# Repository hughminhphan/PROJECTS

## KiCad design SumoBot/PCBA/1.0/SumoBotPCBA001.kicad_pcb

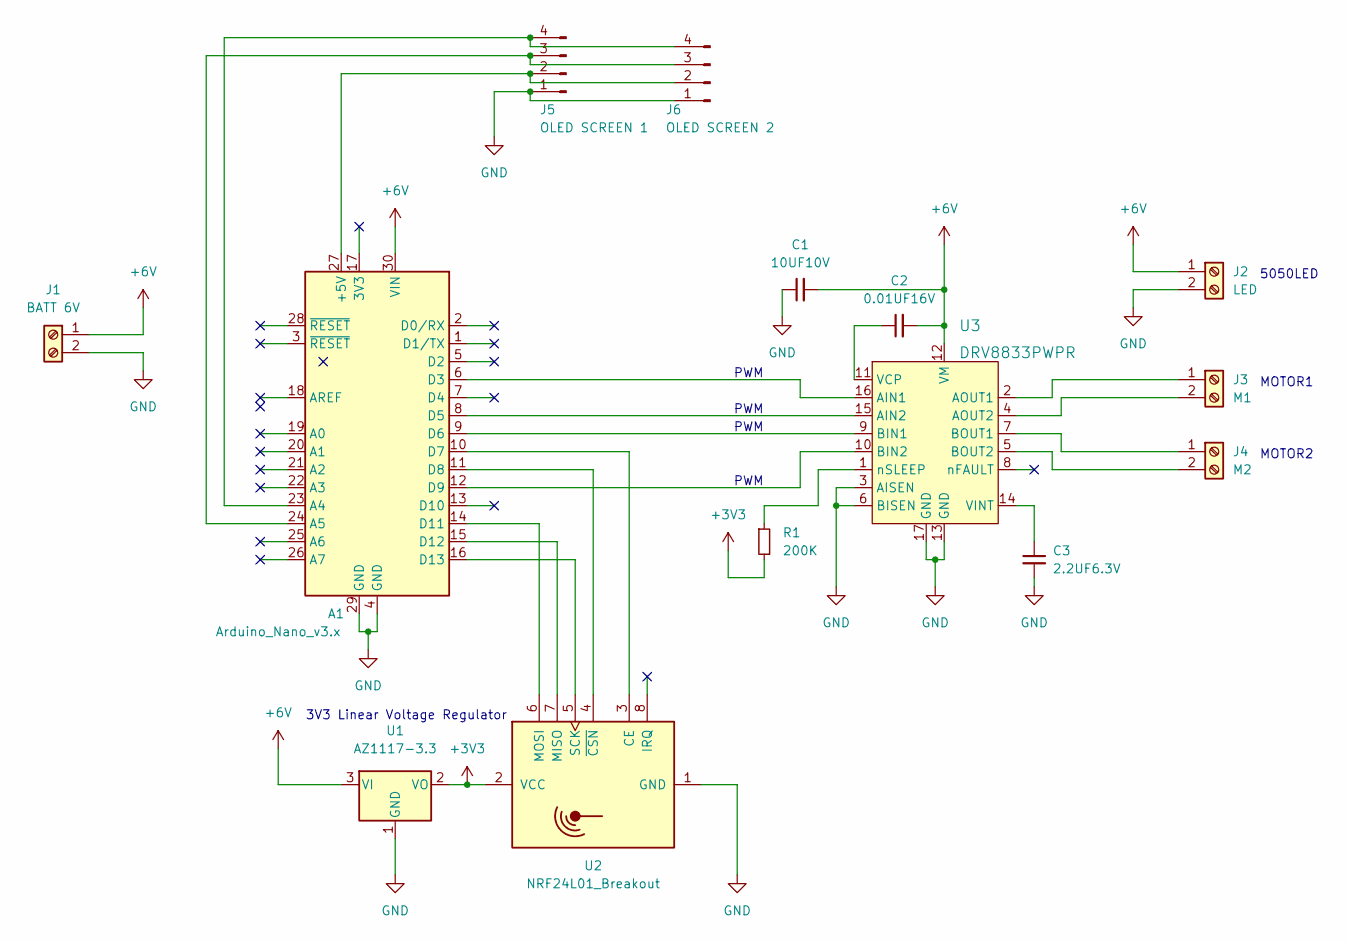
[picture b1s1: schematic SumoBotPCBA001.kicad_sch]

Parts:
A1: Arduino_Nano_v3.x; Arduino_Nano
C1: 10UF10V; C_0805_2012Metric_Pad1.18x1.45mm_HandSolder
C2: 0.01UF16V; C_0805_2012Metric_Pad1.18x1.45mm_HandSolder
C3: 2.2UF6.3V; C_0805_2012Metric_Pad1.18x1.45mm_HandSolder
J1: BATT 6V; TerminalBlock_bornier-2_P5.08mm
J2: LED; TerminalBlock_bornier-2_P5.08mm
J3: M1; TerminalBlock_bornier-2_P5.08mm
J4: M2; TerminalBlock_bornier-2_P5.08mm
J5: OLED SCREEN 1; PinSocket_1x04_P2.54mm_Vertical
J6: OLED SCREEN 2; PinSocket_1x04_P2.54mm_Vertical
R1: 200K; R_0805_2012Metric_Pad1.20x1.40mm_HandSolder
U1: AZ1117-3.3; SOT-89-3_Handsoldering
U2: NRF24L01_Breakout; nRF24L01_Breakout
U3: DRV8833PWPR; TSSOP-16-1EP_W4.40mm; MPN DRV8833PWPR; Digi-Key_PN 296-29434-1-ND

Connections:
+3V3: R1.2, U1.2 (VO), U2.2 (VCC)
+6V: A1.30 (VIN), C1.2, C2.2, J1.1, J2.1, U1.3 (VI), U3.12 (VM)
GND: A1.4 (GND), A1.29 (GND), C1.1, C3.2, J1.2, J2.2, J5.1, J6.1, U1.1 (GND), U2.1 (GND), U3.3 (AISEN), U3.6 (BISEN), U3.13 (GND), U3.17 (GND)
unnamed: A1.6 (D3), U3.16 (AIN1)
unnamed: A1.8 (D5), U3.15 (AIN2)
unnamed: A1.9 (D6), U3.9 (BIN1)
unnamed: A1.10 (D7), U2.3 (CE)
unnamed: A1.11 (D8), U2.4 (~CSN)
unnamed: A1.12 (D9), U3.10 (BIN2)
unnamed: A1.14 (D11), U2.6 (MOSI)
unnamed: A1.15 (D12), U2.7 (MISO)
unnamed: A1.16 (D13), U2.5 (SCK)
unnamed: A1.23 (A4), J5.4, J6.4
unnamed: A1.24 (A5), J5.3, J6.3
unnamed: A1.27 (+5V), J5.2, J6.2
unnamed: C2.1, U3.11 (VCP)
unnamed: C3.1, U3.14 (VINT)
unnamed: J3.1, U3.2 (AOUT1)
unnamed: J3.2, U3.4 (AOUT2)
unnamed: J4.1, U3.7 (BOUT1)
unnamed: J4.2, U3.5 (BOUT2)
unnamed: R1.1, U3.1 (nSLEEP)

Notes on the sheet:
PWM
5050LED
MOTOR1
MOTOR2
3V3 Linear Voltage Regulator

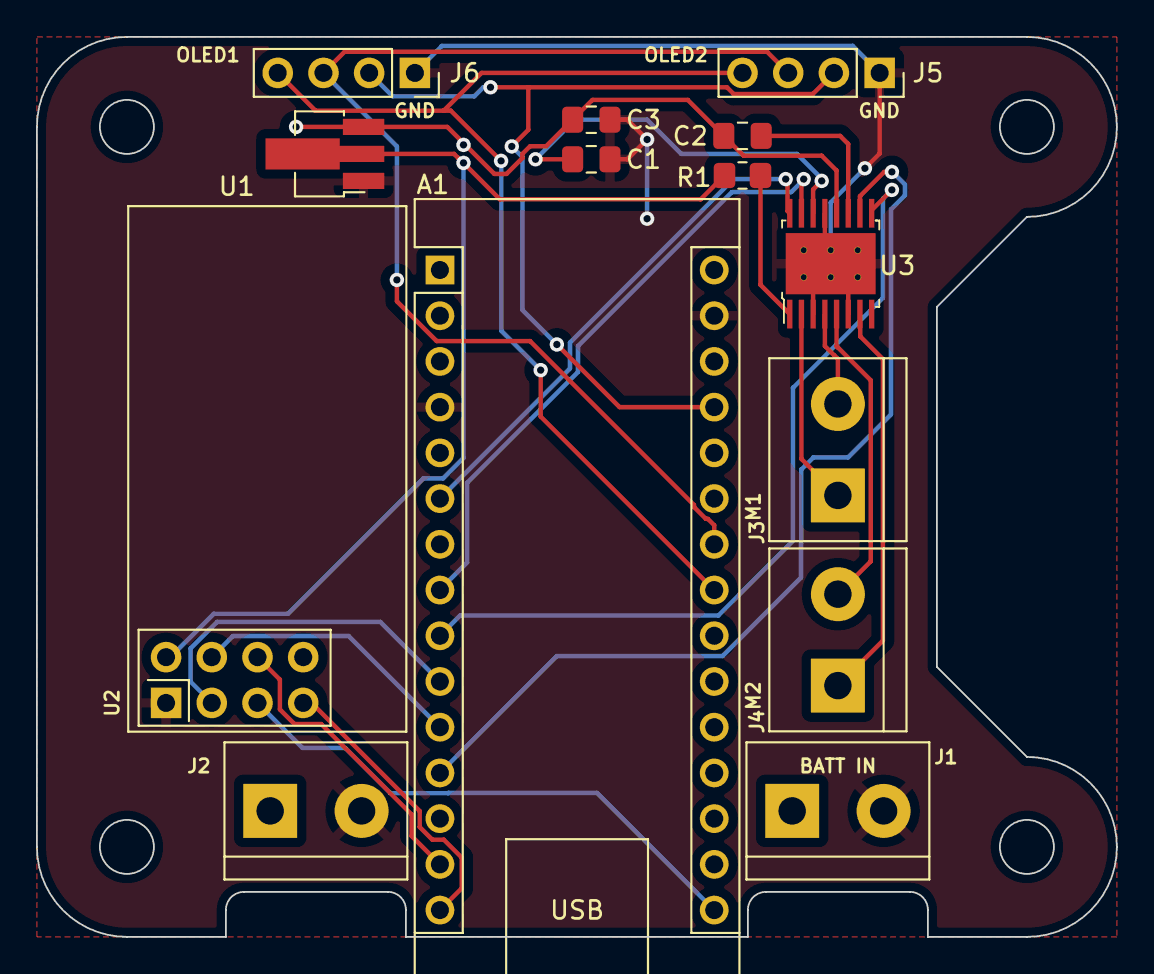
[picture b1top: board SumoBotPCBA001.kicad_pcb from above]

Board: 2 copper layers, 60.0 x 50.0 mm, 14 parts (0 on the bottom side), 22 nets.

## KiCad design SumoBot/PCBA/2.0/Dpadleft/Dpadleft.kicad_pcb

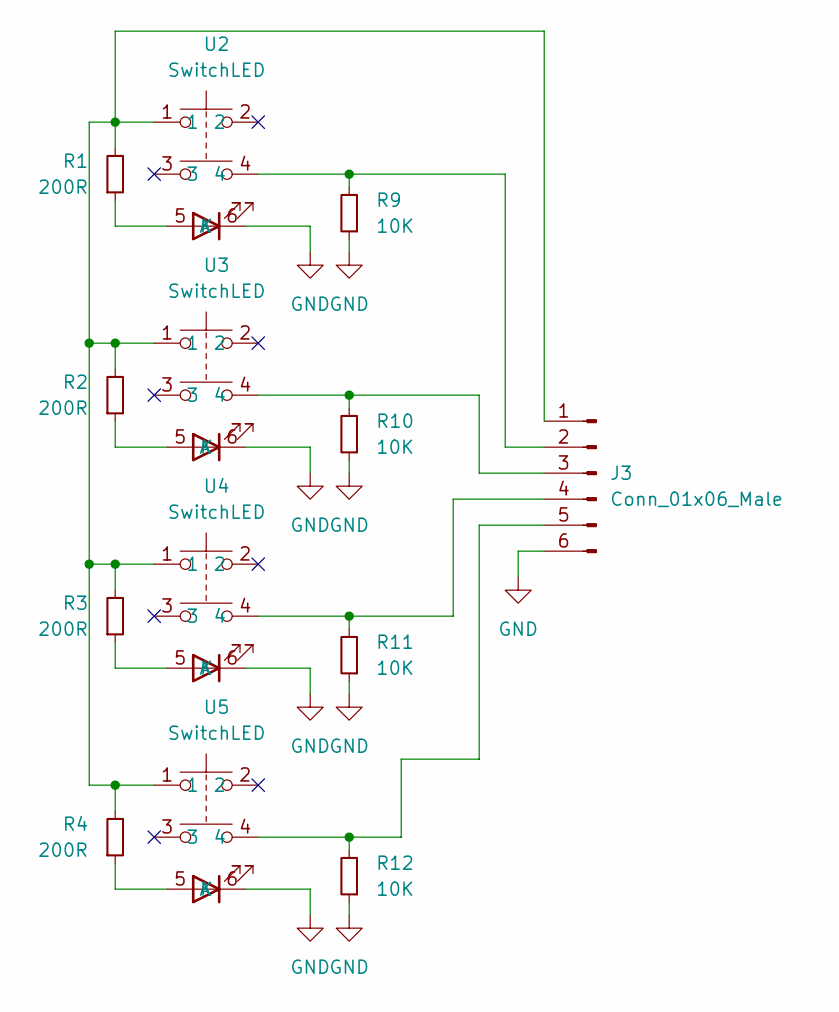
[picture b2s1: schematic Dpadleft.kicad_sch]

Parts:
J3: Conn_01x06_Male; PinHeader_1x06_P2.54mm_Vertical
R1, R2, R3, R4: 200R; R_0402_1005Metric
R9, R10, R11, R12: 10K; R_0402_1005Metric
U2, U3, U4, U5: SwitchLED

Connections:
GND: J3.6, R9.1, R10.1, R11.1, R12.1, U2.6 (K), U3.6 (K), U4.6 (K), U5.6 (K)
unnamed: J3.1, R1.2, R2.2, R3.2, R4.2, U2.1, U3.1, U4.1, U5.1
unnamed: J3.2, R9.2, U2.4
unnamed: J3.3, R10.2, U3.4
unnamed: J3.4, R11.2, U4.4
unnamed: J3.5, R12.2, U5.4
unnamed: R1.1, U2.5 (A)
unnamed: R2.1, U3.5 (A)
unnamed: R3.1, U4.5 (A)
unnamed: R4.1, U5.5 (A)

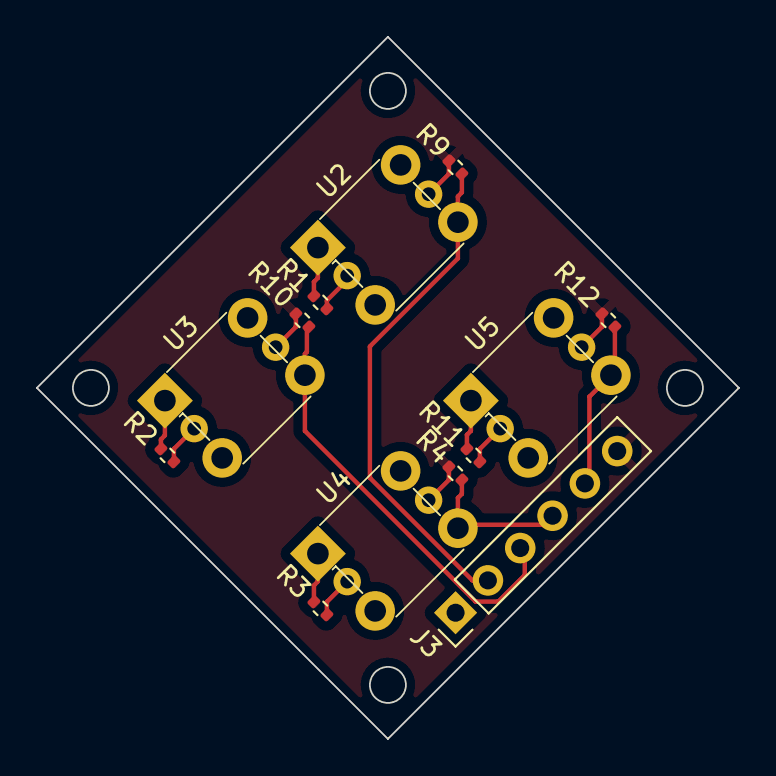
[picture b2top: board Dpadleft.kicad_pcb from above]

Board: 2 copper layers, 39.0 x 39.0 mm, 13 parts (0 on the bottom side), 10 nets.

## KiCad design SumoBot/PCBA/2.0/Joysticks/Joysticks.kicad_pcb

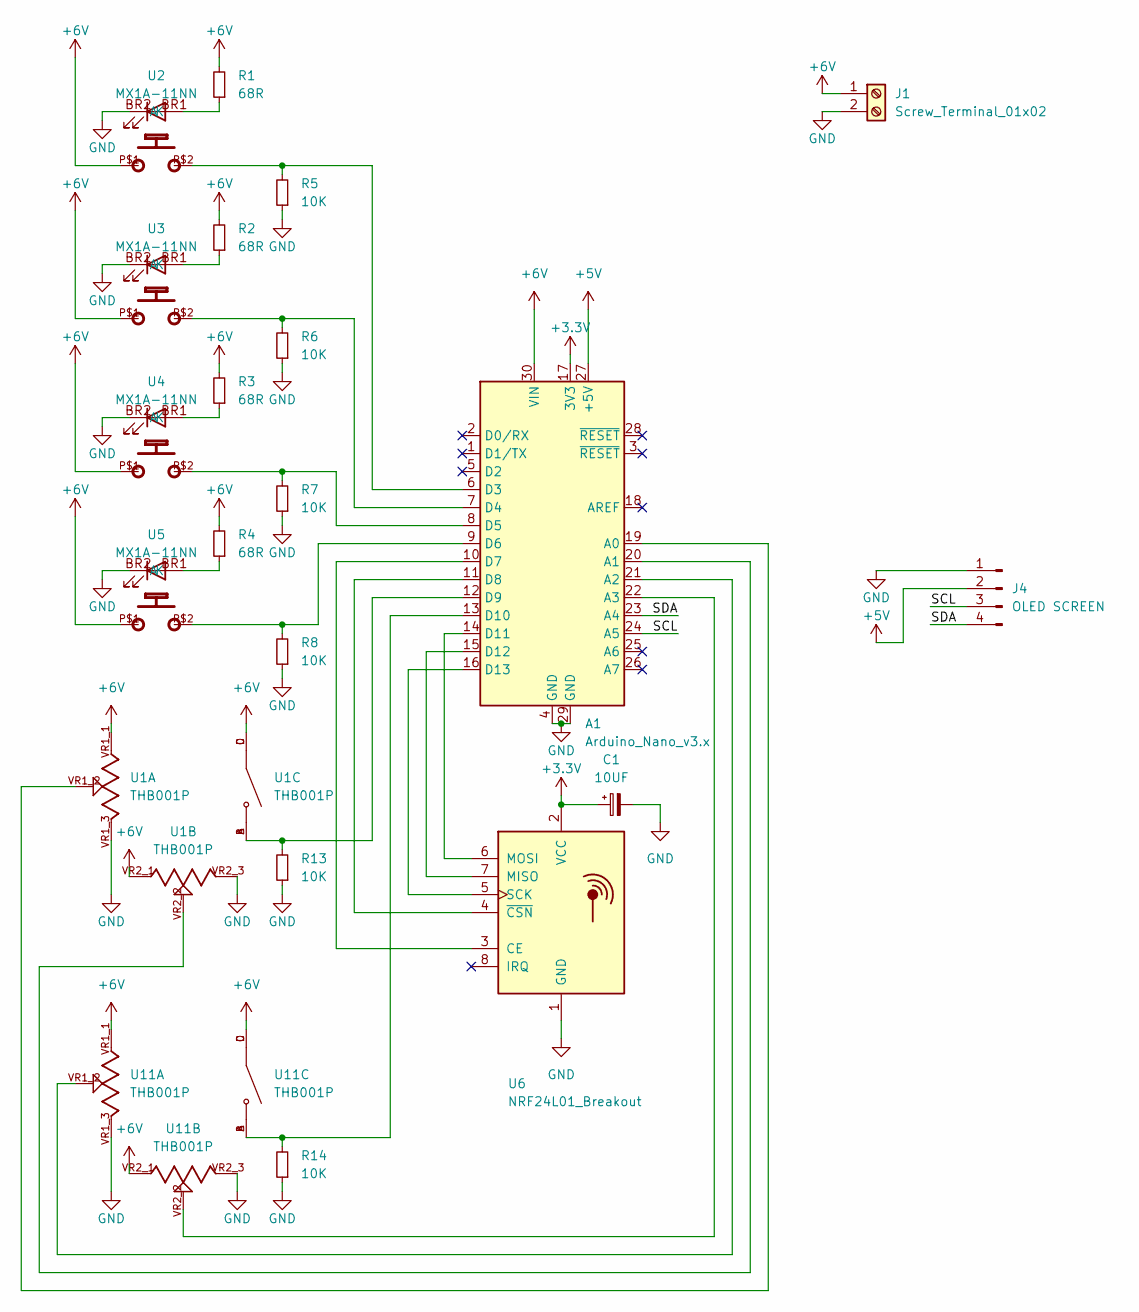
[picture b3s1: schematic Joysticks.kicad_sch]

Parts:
A1: Arduino_Nano_v3.x; Arduino_Nano
C1: 10UF; C_0805_2012Metric
J1: Screw_Terminal_01x02; TerminalBlock_TE_282834-2_1x02_P2.54mm_Horizontal
J4: OLED SCREEN; PinSocket_1x04_P2.54mm_Vertical
R1, R2, R3, R4: 68R; R_0805_2012Metric
R5, R6, R7, R8, R13, R14: 10K; R_0805_2012Metric
U1, U11: THB001P; CNK_THB001P; PARTREV 27 Jan 22
U2, U3, U4, U5: MX1A-11NN; CHERRY_MX1A-11NN_SWITCH
U6: NRF24L01_Breakout; nRF24L01_Breakout_SMD

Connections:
+3.3V: A1.17 (3V3), C1.1, U6.2 (VCC)
+5V: A1.27 (+5V), J4.2
+6V: A1.30 (VIN), J1.1, R1.2, R2.2, R3.2, R4.2, U1.C, U1.D, U1.VR1_1, U1.VR2_1, U2.P$1, U3.P$1, U4.P$1, U5.P$1, U11.C, U11.D, U11.VR1_1, U11.VR2_1
/SCL: A1.24 (A5), J4.3
/SDA: A1.23 (A4), J4.4
GND: A1.4 (GND), A1.29 (GND), C1.2, J1.2, J4.1, R5.1, R6.1, R7.1, R8.1, R13.1, R14.1, U1.VR1_3, U1.VR2_3, U2.BR2 (K), U3.BR2 (K), U4.BR2 (K), U5.BR2 (K), U6.1 (GND), U11.VR1_3, U11.VR2_3
unnamed: A1.6 (D3), R5.2, U2.P$2
unnamed: A1.7 (D4), R6.2, U3.P$2
unnamed: A1.8 (D5), R7.2, U4.P$2
unnamed: A1.9 (D6), R8.2, U5.P$2
unnamed: A1.10 (D7), U6.3 (CE)
unnamed: A1.11 (D8), U6.4 (~CSN)
unnamed: A1.12 (D9), R13.2, U1.A, U1.B
unnamed: A1.13 (D10), R14.2, U11.A, U11.B
unnamed: A1.14 (D11), U6.6 (MOSI)
unnamed: A1.15 (D12), U6.7 (MISO)
unnamed: A1.16 (D13), U6.5 (SCK)
unnamed: A1.19 (A0), U1.VR1_2
unnamed: A1.20 (A1), U1.VR2_2
unnamed: A1.21 (A2), U11.VR1_2
unnamed: A1.22 (A3), U11.VR2_2
unnamed: R1.1, U2.BR1 (A)
unnamed: R2.1, U3.BR1 (A)
unnamed: R3.1, U4.BR1 (A)
unnamed: R4.1, U5.BR1 (A)

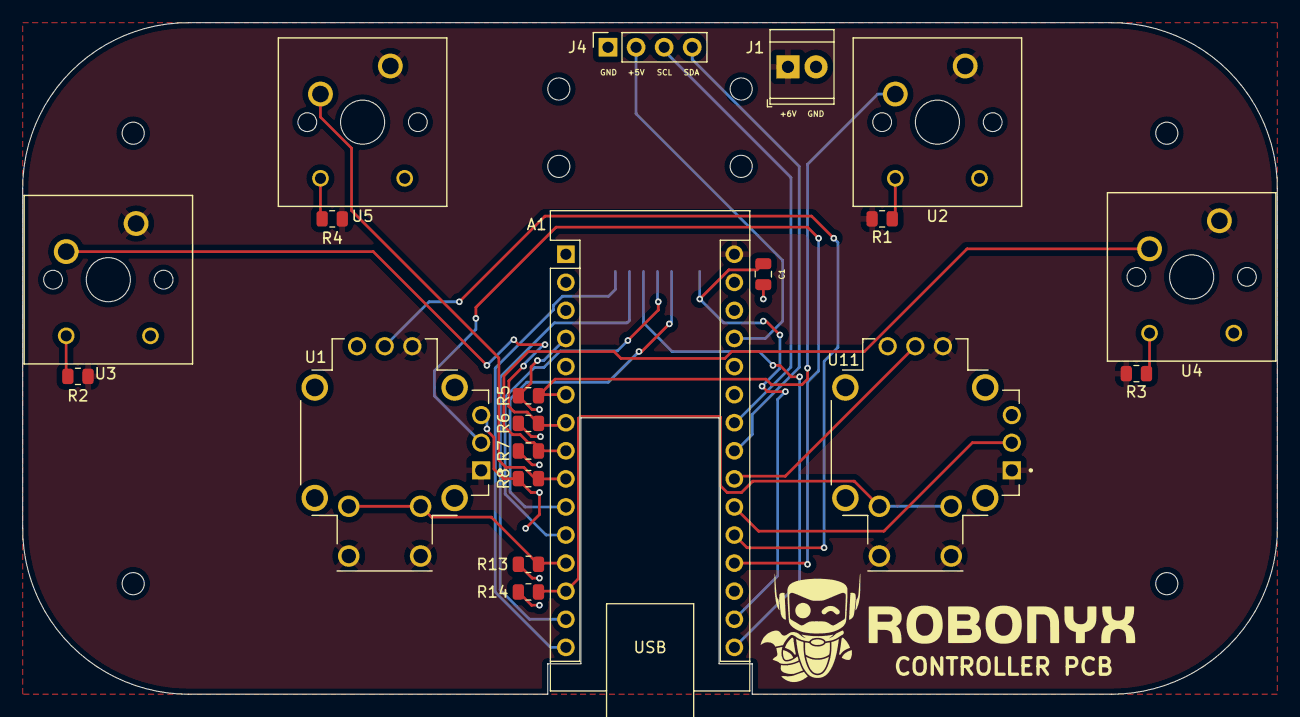
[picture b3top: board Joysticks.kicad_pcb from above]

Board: 2 copper layers, 113.5 x 60.8 mm, 21 parts (1 on the bottom side), 25 nets.

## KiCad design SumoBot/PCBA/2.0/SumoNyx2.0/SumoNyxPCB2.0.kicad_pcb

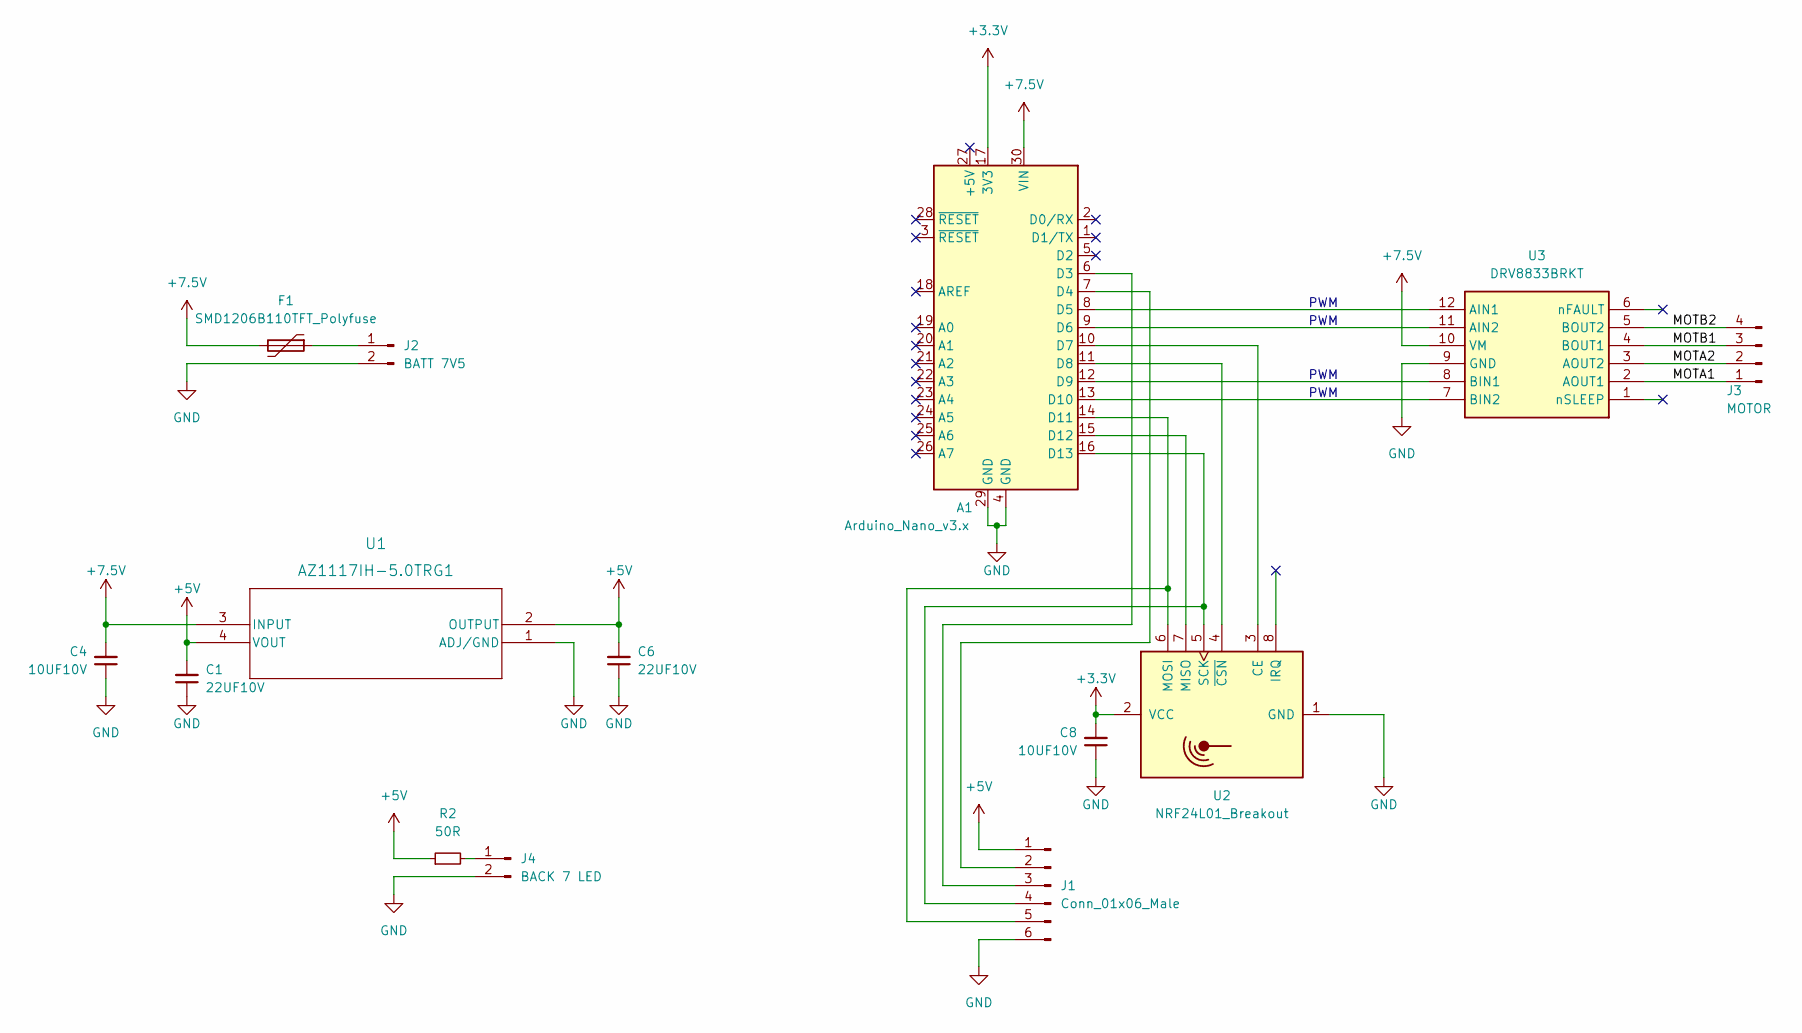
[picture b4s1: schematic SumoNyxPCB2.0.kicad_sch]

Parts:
A1: Arduino_Nano_v3.x; Arduino_Nano
C1, C6: 22UF10V; C_0805_2012Metric_Pad1.18x1.45mm_HandSolder
C4, C8: 10UF10V; C_0805_2012Metric_Pad1.18x1.45mm_HandSolder
F1: SMD1206B110TFT_Polyfuse; Fuse_1206_3216Metric
J1: Conn_01x06_Male; PinHeader_1x06_P2.54mm_Vertical
J2: BATT 7V5; PinHeader_1x02_P2.54mm_Vertical
J3: MOTOR; PinSocket_1x04_P2.54mm_Vertical
J4: BACK 7 LED; PinHeader_1x02_P2.54mm_Vertical
R2: 50R; R_0805_2012Metric
U1: AZ1117IH-5.0TRG1; SOT223-5_DIO
U2: NRF24L01_Breakout; nRF24L01_Breakout_SMD
U3: DRV8833BRKT

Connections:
+3.3V: A1.17 (3V3), C8.2, U2.2 (VCC)
+5V: C1.2, C6.2, J1.1, R2.1, U1.2 (OUTPUT), U1.4 (VOUT)
+7.5V: A1.30 (VIN), C4.2, F1.2, U1.3 (INPUT), U3.10 (VM)
/MOTA1: J3.1, U3.2 (AOUT1)
/MOTA2: J3.2, U3.3 (AOUT2)
/MOTB1: J3.3, U3.4 (BOUT1)
/MOTB2: J3.4, U3.5 (BOUT2)
GND: A1.4 (GND), A1.29 (GND), C1.1, C4.1, C6.1, C8.1, J1.6, J2.2, J4.2, U1.1 (ADJ/GND), U2.1 (GND), U3.9 (GND)
unnamed: A1.6 (D3), J1.3
unnamed: A1.7 (D4), J1.2
unnamed: A1.8 (D5), U3.12 (AIN1)
unnamed: A1.9 (D6), U3.11 (AIN2)
unnamed: A1.10 (D7), U2.3 (CE)
unnamed: A1.11 (D8), U2.4 (~CSN)
unnamed: A1.12 (D9), U3.8 (BIN1)
unnamed: A1.13 (D10), U3.7 (BIN2)
unnamed: A1.14 (D11), J1.5, U2.6 (MOSI)
unnamed: A1.15 (D12), U2.7 (MISO)
unnamed: A1.16 (D13), J1.4, U2.5 (SCK)
unnamed: F1.1, J2.1
unnamed: J4.1, R2.2

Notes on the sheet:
PWM

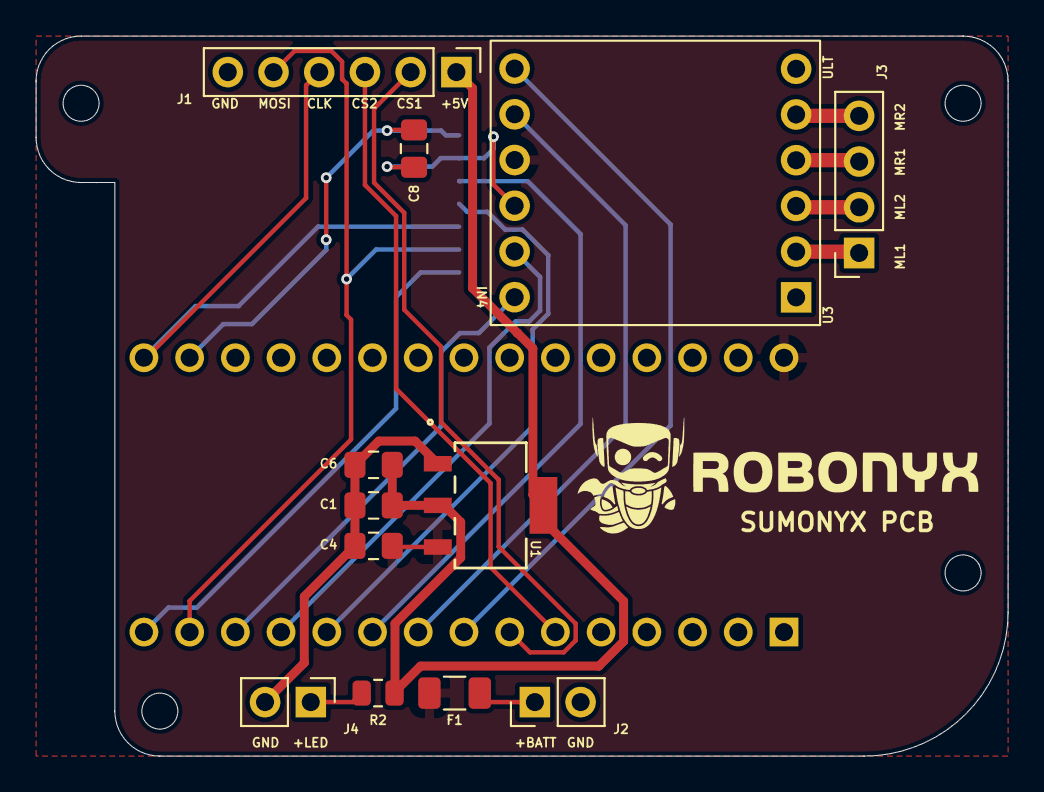
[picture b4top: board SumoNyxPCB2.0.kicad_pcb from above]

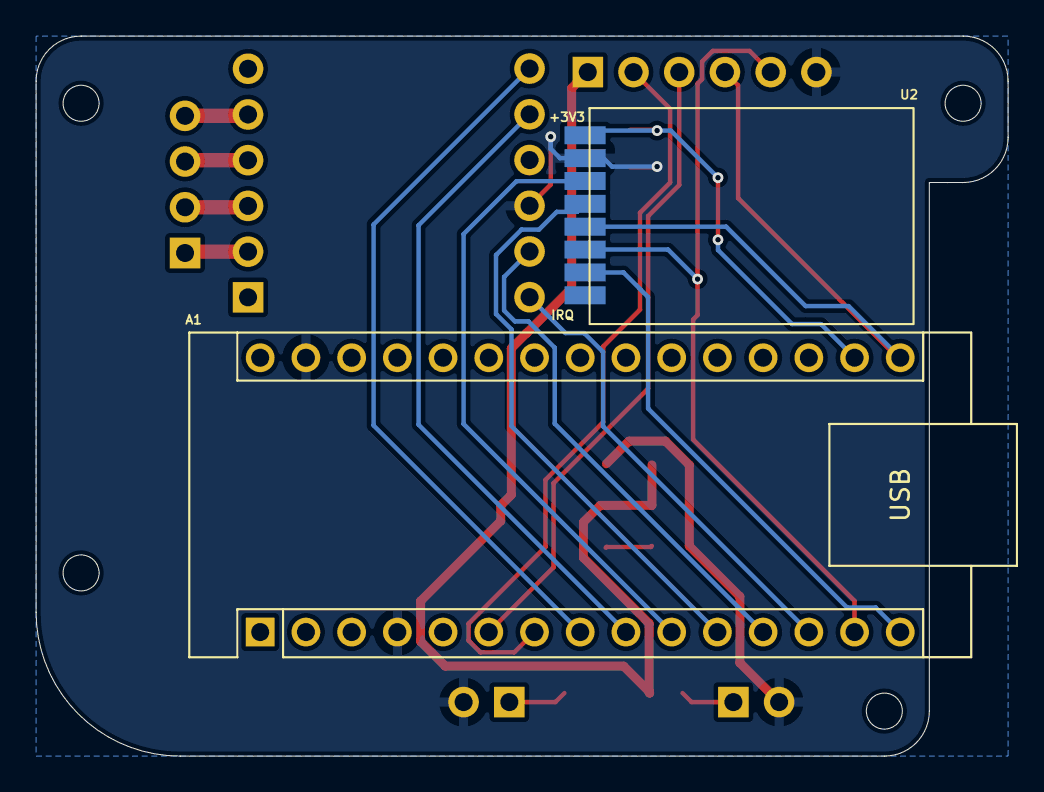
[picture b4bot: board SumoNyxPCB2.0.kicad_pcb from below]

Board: 2 copper layers, 54.0 x 40.0 mm, 14 parts (2 on the bottom side), 21 nets.
